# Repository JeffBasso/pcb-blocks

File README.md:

# pcb-blocks

Reusable circuit blocks for KiCad 10. Each block is a SKiDL Python module (the checked list of
parts and nets) paired with a KiCad design block (the drawn sheet), and the two are checked against
each other.

**Status: drawn and parity-checked; not yet bench-proven. No compliance certification
(IEEE 802.3bt, safety or EMC) is claimed.** A block counts as proven only when its BRINGUP.md has
measurements from a built board. Until then it's a reviewed design, not a tested one.

## Blocks

| Block | What it is | Proven on | Status |
|---|---|---|---|
| [`poe_pd`](blocks/poe_pd/BLOCK.md) | IEEE 802.3bt PoE PD front end (ADI DC2583A design): LT4321 ideal-diode bridge, CM choke and TVS, LT4294 (Class 8) with a high-side hot-swap FET, T2P grant over an optocoupler; rated for 90 W continuous, no PD current limit | not yet (wallnode-amp rev A) | drawn, parity 0; laid out (2-layer, DRC 0, FET copper sized for 90 W) |

## What's in a block

```
blocks/<name>/
  BLOCK.md                 what it is, its ports and ratings, sources and licence check, where it's proven
  BRINGUP.md               measurements from built boards (empty until it's built)
  src/blocks/<name>.py     the SKiDL module a board copies: @subcircuit <name>(ports...)
  src/<name>.py            test harness: wires the ports to named nets for the parity check
  <name>.kicad_sch         test project's top sheet: the block as one sheet, its ports to global labels
  <name>_sheet.kicad_sch   the drawn block
  <name>.png               the drawn block, for reading without KiCad
  <name>.kicad_pcb         the block's layout (optional): the test project's board, with an outline for DRC
  <name>.kicad_dru         that board's design rules
  layout_<name>.py         the script that makes the layout (pcbnew Python), if it was made by script
  <name>_layout.png        the layout, for reading without KiCad
pcb-blocks.kicad_blocks/<name>.kicad_block/
  <name>.kicad_sch         KiCad design block: a byte-identical copy of <name>_sheet.kicad_sch
  <name>.kicad_pcb         the layout: <name>.kicad_pcb without its outline (tools/block_layout.py)
  <name>.json              its description, keywords and fields
lib/pcb-blocks.kicad_sym, lib/pcb-blocks.pretty/   symbols and footprints the blocks need beyond KiCad's own
```

## Using a block

With the [PCB design kit](https://github.com/JeffBasso/pcb-design-kit) installed, this repo is cloned
to `C:\dev\pcb\blocks`, and `pcb-blocks` is already in KiCad's design-block, symbol and footprint
tables. Without the kit, add those three yourself, pointing at this checkout.

1. Place the block from KiCad's Design Blocks panel as its own sheet.
2. Copy `blocks/<name>/src/blocks/<name>.py` into your board's SKiDL `src/blocks/`, with a first line
   `# from pcb-blocks <tag or main> (<commit>)` so you know which version you took.
3. Call it from your `board()` with your nets, and check the drawing and the Python agree (the kit's
   `pcb-skidl.ps1 <board> -Sheet "<sheet name>"`).
4. If the block has a layout, bring it onto your board as one group (KiCad applies a design block's
   layout when the PCB is updated from the schematic; headless, copy positions and copper by reference).
   It uses F.Cu and B.Cu only; your board's inner planes, pours and isolation barrier stay yours.

Pin to a commit: a later change here doesn't change your board. Blocks get tags (`poe-pd-v1.0`)
once they're bench-proven.

## Adding a block

1. Draw it and prove it on a board. It needs a code-first board (Python and drawing at parity 0)
   and bench measurements.
2. Cut its sheet out of the board with `tools/cut_sheet.py`, which also writes the test project's
   top sheet. Copy the board's module into `src/blocks/`, and write the harness `src/<name>.py`.
3. Copy `<name>_sheet.kicad_sch` into `pcb-blocks.kicad_blocks/<name>.kicad_block/<name>.kicad_sch`,
   and write `<name>.json`.
4. Run `tools\check-blocks.ps1` until every block passes. Then run the kit's
   `pcb-sch-junctions.ps1 blocks\<name> -Check` and `kicad-cli sch erc` on the block project, both
   with 0 errors.
5. Write BLOCK.md (all seven sections, and section 9 for a layout) and BRINGUP.md, and open a pull
   request.
6. Optional layout: make the test project's board (`blocks/<name>/<name>.kicad_pcb`, DRC 0), then
   `python tools/block_layout.py copy . <name>` to put it in the design block.

The drawing and the Python change together, in the same commit, with `check-blocks.ps1` passing.

## Tools

- `tools/cut_sheet.py`: cuts a block out of a drawn sheet and refuses an unclean cut. Run it with the
  kit's SKiDL venv python, or any Python 3.10+. Tests: `python -m unittest discover -s tools`.
- `tools/block_layout.py`: writes (`copy`) and checks (`check`) a block's layout in its design block -
  the test project's board without its Edge.Cuts outline. Any Python 3.10+.
- `tools/check-blocks.ps1`: parity, the design-block copy check and, for a block with a layout, the
  layout copy check, for every block. Needs the kit's `pcb-skidl.ps1` (`-Kit <folder>`, default
  `C:\dev\pcb`) and `python` on PATH. Tests: `tools/check-blocks.Tests.ps1` (Pester 5 or later).

## Licence

CERN Open Hardware Licence Version 2 - Permissive (CERN-OHL-P-2.0). See [LICENSE](LICENSE). Each
block's BLOCK.md records the sources it draws on and their terms. KiCad's stock symbols and
footprints are CC-BY-SA-4.0 with KiCad's exception for designs that use them.

The blocks are provided as is, with no warranty. You're responsible for checking a block against your
own requirements and for any certification your product needs.

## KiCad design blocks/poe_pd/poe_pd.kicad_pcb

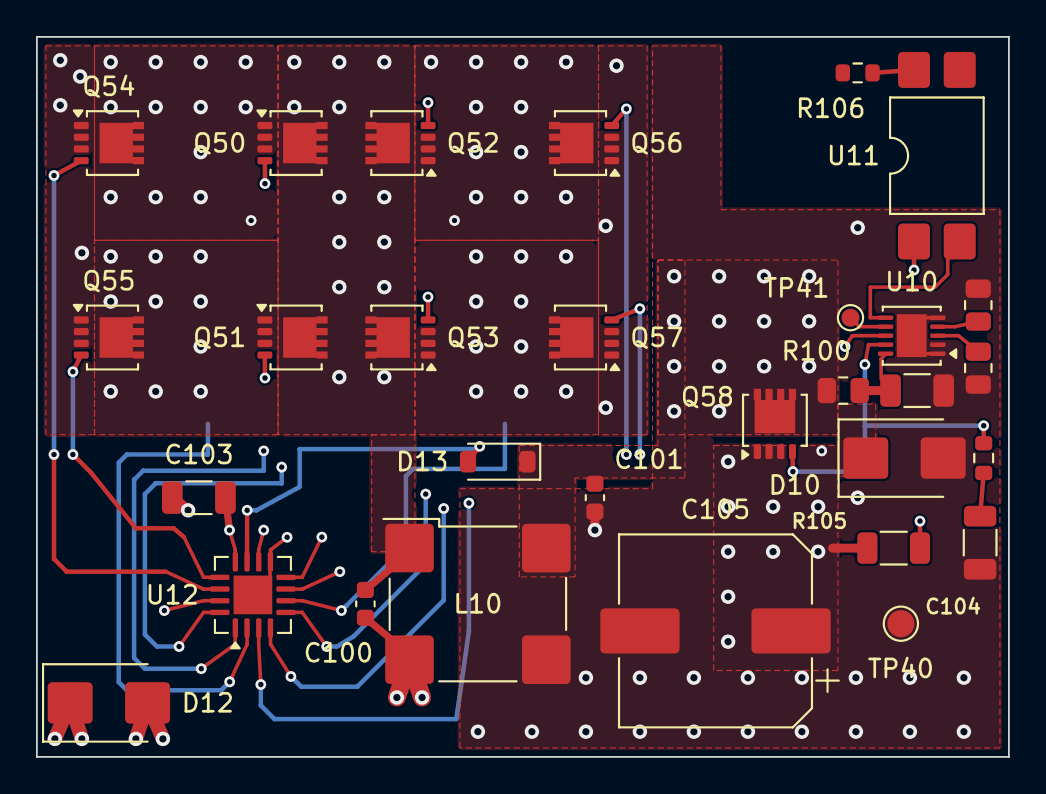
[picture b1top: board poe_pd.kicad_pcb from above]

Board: 4 copper layers, 54.0 x 40.0 mm, 30 parts (0 on the bottom side), 27 nets.

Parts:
C100, C101: 1nF/250V; C_0603_1608Metric
C102, C103, C104: 47nF/250V; C_1206_3216Metric
C105: 100uF/100V VKME1452A101MV; CP_Elec_10x14.3
D10, D12: SMBJ58A; D_SMB
D13: MMSZ5252B 24V; D_SOD-123
L10: 250uH 744272251; L_CommonModeChoke_Wuerth_WE-SL5
Q50, Q51, Q52, Q53, Q54, Q55, Q56, Q57, Q58: PSMN040-100MSE; LFPAK33
R100: 8.2R; R_0805_2012Metric
R101: 49.9R 1%; R_0805_2012Metric
R102: 118R 1% (Class 8); R_0805_2012Metric
R103: 3.3k; R_0603_1608Metric
R105: 33k; R_1206_3216Metric
R106: 10k; R_0603_1608Metric
TP40: POE_VSS (primary!); TestPoint_Pad_D1.5mm
TP41: PD_PWRGD (primary!); TestPoint_Pad_D1.0mm
U10: LT4294HDD#PBF; DFN-10-1EP_3x3mm_P0.5mm_EP1.65x2.38mm
U11: FOD817AS; SMDIP-4_W9.53mm
U12: LT4321HUF#PBF; QFN-16-1EP_4x4mm_P0.65mm_EP2.15x2.15mm

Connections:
/PoE PD/BR_N: C100.2, C103.2, D12.2, L10.3, Q54.1, Q54.2, Q54.3, Q55.1, Q55.2, Q55.3, Q56.1, Q56.2, Q56.3, Q57.1, Q57.2, Q57.3, U12.9, U12.17
/PoE PD/BR_P: C100.1, C103.1, D12.1, L10.2, Q50.5, Q51.5, Q52.5, Q53.5, U12.10, U12.12
/PoE PD/PD_BG12: Q54.4, U12.14
/PoE PD/PD_BG36: Q55.4, U12.13
/PoE PD/PD_BG45: Q56.4, U12.8
/PoE PD/PD_BG78: Q57.4, U12.7
/PoE PD/PD_BR_EN: D13.2, U12.11
/PoE PD/PD_CGATE: C104.1, R103.2
/PoE PD/PD_HSGATE: Q58.4, R103.1, U10.9
/PoE PD/PD_RCLS: R101.1, U10.3
/PoE PD/PD_RCLSPP: R102.1, U10.4
/PoE PD/PD_T2P: U10.6, U11.2
/PoE PD/PD_TG12: Q50.4, U12.16
/PoE PD/PD_TG36: Q51.4, U12.1
/PoE PD/PD_TG45: Q52.4, U12.4
/PoE PD/PD_TG78: Q53.4, U12.5
/PoE PD/PD_VPIN: C102.1, R100.2, U10.10
/PoE PD/PD_VPORT: C101.1, D10.1, D13.1, L10.1, Q58.5, R100.1
/PoE PD/T2P_LED_A: R105.2, U11.1
PD_PWRGD: TP41.1, U10.7
POE_T2P_N: R106.2, U11.4
POE_VDD: C105.1, Q58.1, Q58.2, Q58.3, R105.1, U10.8
POE_VSS: C101.2, C102.2, C104.2, C105.2, D10.2, L10.4, R101.2, R102.2, TP40.1, U10.1, U10.2, U10.5, U10.11
PR12: Q50.1, Q50.2, Q50.3, Q54.5, U12.15
PR36: Q51.1, Q51.2, Q51.3, Q55.5, U12.2
PR45: Q52.1, Q52.2, Q52.3, Q56.5, U12.3
PR78: Q53.1, Q53.2, Q53.3, Q57.5, U12.6

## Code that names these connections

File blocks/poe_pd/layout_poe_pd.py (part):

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    PR45 on In2 in the same gaps. All come down to the LT4321 (U12) below the bridge, which has a ring of fan-out vias
    5 mm out. Its pins run in roughly the reverse order of the bridge's signals, so the west group winds round it
    counter-clockwise (F.Cu: BG36, BG12; B.Cu: TG12, TG36, PR36; In2: PR12) and the east group clockwise (B.Cu: PR78,
    TG78, TG45, PR45; In1: BG45, BG78), each layer keeping its own order.
  - Bottom strip, y 22-40: U12 with C103 and its TVS D12; C100 and the choke L10, whose BR_P input sits on an F.Cu
    extension of the BR_P column. Under the bridge side, In1 is a BR_N plane and In2 a BR_P plane.
  - Right column, x 34.5-54: the PD. The VPORT square (Q58's tab, all layers) fed from L10.1 by an F.Cu leg that
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LID = {'F.Cu': pcbnew.F_Cu, 'In1.Cu': pcbnew.In1_Cu, 'In2.Cu': pcbnew.In2_Cu, 'B.Cu': pcbnew.B_Cu}

BR_P, BR_N = '/PoE PD/BR_P', '/PoE PD/BR_N'
VPORT, VPIN = '/PoE PD/PD_VPORT', '/PoE PD/PD_VPIN'
VSS, VDD, PWRGD = 'POE_VSS', 'POE_VDD', 'PD_PWRGD'
P_ = lambda n: '/PoE PD/' + n
TG = lambda p: P_('PD_TG' + p)
BG = lambda p: P_('PD_BG' + p)
EN, HSG, CG, T2P, LED = P_('PD_BR_EN'), P_('PD_HSGATE'), P_('PD_CGATE'), P_('PD_T2P'), P_('T2P_LED_A')
POE_IN = {VDD, VSS, BR_P, BR_N, VPORT, VPIN, 'PR12', 'PR36', 'PR45', 'PR78'}

# --- bridge geometry ---------------------------------------------------------------------------------------
X_BRNL, X_CL, X_BRP, X_CR, X_BRNR, X_END = 0.5, 3.2, 13.4, 21.0, 31.2, 33.9
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T(BR_P, 'F.Cu', 0.4, (10.7, UY - 3.6), ('C103', '1'))
T(EN, 'F.Cu', W_SIG, S('U12', '11'), (11.68, UY - 4.7)); V(EN, (11.68, UY - 4.7))
T(BR_P, 'F.Cu', 0.2, S('U12', '10'), (12.32, UY - 2.5), (12.6, UY - 3.6)); V(BR_P, (12.6, UY - 3.6), SM)
T(BR_N, 'F.Cu', 0.2, (12.95, UY - 1.4), (12.95, UY - 0.8))                               # pin 9 into the exposed pad
T(BR_N, 'F.Cu', 0.2, S('U12', '9'), (12.98, UY - 2.5), (13.9, UY - 3.2)); V(BR_N, (13.9, UY - 3.2), SM)
V(BR_N, (8.4, 26.3)); T(BR_N, 'F.Cu', 0.6, ('C103', '2'), (8.4, 26.3))

# --- U12's signals from the bridge to the ring ------------------------------------------------------------------
# The LT4321's pins run in roughly the reverse order of the bridge's signals, so the two groups wind round U12 the
# opposite ways, each layer keeping its own order: west side CCW (B.Cu: TG12 inside, TG36, PR36 outside; F.Cu:
# BG36, BG12), east side CW (B.Cu: PR78 inside, TG78, TG45, PR45 outside; In1: BG45, BG78).
T(BG('36'), 'F.Cu', W_SIG, (2.0, 23.2), (3.0, 24.2), (5.5, 27.3), (7.6, 27.3), RV[BG('36')])
T(BG('12'), 'F.Cu', W_SIG, (0.95, 23.2), (0.95, 29.0), (1.66, 29.71), RV[BG('12')])
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

# Conducting FETs in the one-pair-set worst case (calc/poe_pd_90w.py): every top FET (one at a time, on the shared
# BR_P column), every bottom FET (on its own cell), and Q58. (ref, label, neighbour within ~2 mm conducting)
COPPER_FETS = [('Q50', 'Q50-Q53 top (BR_P column, shared)'), ('Q54', 'Q54 bottom, PR12 cell'),
               ('Q55', 'Q55 bottom, PR36 cell'), ('Q56', 'Q56 bottom, PR45 cell'), ('Q57', 'Q57 bottom, PR78 cell'),
               ('Q58', 'Q58 hot-swap (VPORT square)')]
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
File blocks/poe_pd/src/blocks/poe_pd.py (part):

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    """
    br_p, br_n = Net('BR_P'), Net('BR_N')             # LT4321 OUTP / OUTN, before the choke
    vport = Net('PD_VPORT')                            # after the choke, ahead of the hot-swap FET
    vpin = Net('PD_VPIN')                              # the LT4294 VPORT pin, behind its 8.2 ohm
    br_en = Net('PD_BR_EN')
    hsgate, cgate = Net('PD_HSGATE'), Net('PD_CGATE')
    rcls, rclspp = Net('PD_RCLS'), Net('PD_RCLSPP')
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    r100 = R('R100', '8.2R', 'CRCW08058R20JNEA', R_0805)
    r100[1, 2] += vport, vpin
    c102 = C('C102', '47nF/250V', C_1206, mpn='CC1206KKX7RYBB473')
    c102[1, 2] += vpin, POE_VSS

    # source: LT4294 Rev B p2/p5 (pinout), p16 (typical application), DC2583A p8 (U1).
    u10 = Part('pcb-blocks', 'LT4294', ref='U10', value='LT4294HDD#PBF',
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
    pwr_flag(POE_VSS)
    pwr_flag(vpin)          # the LT4294 VPORT pin, fed through R100 (passive)
    pwr_flag(POE_VDD)       # driven through the hot-swap FET (passive pins)
    for net in (PR12, PR36, PR45, PR78, br_p, br_n):
        pwr_flag(net)       # the LT4321's IN/OUT pins are power inputs; the magnetics and FETs are passive

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

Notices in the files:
blocks/poe_pd/src/blocks/poe_pd.py:
"""poe_pd: IEEE 802.3bt PoE powered-device front end (pcb-blocks, CERN-OHL-P-2.0).
